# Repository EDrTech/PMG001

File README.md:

# PMG001 Power management module

The PMG001 is a highly integrated module designed for efficient management of single-cell
Li-Po battery systems. It incorporates various essential ICs to address all aspects of power
management, including battery charging, switch/button power on/off behavior, undervoltage
and overvoltage protection, flexible voltage measurement, battery current measurement, and
temperature monitoring. Additionally, it features a microcontroller for programming custom
behaviors, ensuring comprehensive management of single-cell rechargeable battery
systems.
Furthermore, when paired with the demo kit base PCB, the module serves as a general
development board for the ATTINY1616, with all
1 pins accessible for any application.

## Features

- 32 PIN 22.22mm *16.51mm package
- On/off behavior control
- 2A single cell charger
- Single li-po cell powered
- 4+16 ADC channels
- Bi-directional battery current measurement
- Brown-out detection/reset circuit
- Low RDSon battery output MOSFET
- On-module temperature measurement
- I2C Interface
- Arduino compatible

## Installation

To program this module you will need the following:

- Arduino DE (Or other IDE of your choosing)
- [megaTinyCore](https://github.com/SpenceKonde/megaTinyCore)
- Demo kit with the module soldered on

There's no need to install any additional libraries as the example code only uses the wire library to handle I2C, the rest is in the [example](pmg001_default/pmg001_default.ino) code. Keep in mind that some register values are hardcoded, which is not the best way to handle something like that but is done here for the sake of simplicity. You can use external libraries with this module without issues, you just need to redefine I2C adresses of devices as they don't necessarily match with other libraries.

Board settings should be set up like this:

Default code provides basic power management and monitoring - press PWR_SW for >500ms and BAT_OUT will turn on, hold PWR_SW for >3s and BAT_OUT will turn off.

For more information, please read the [datasheet](PMG001_datasheet.pdf).

## Module Schematic

## Breakout board Schematic

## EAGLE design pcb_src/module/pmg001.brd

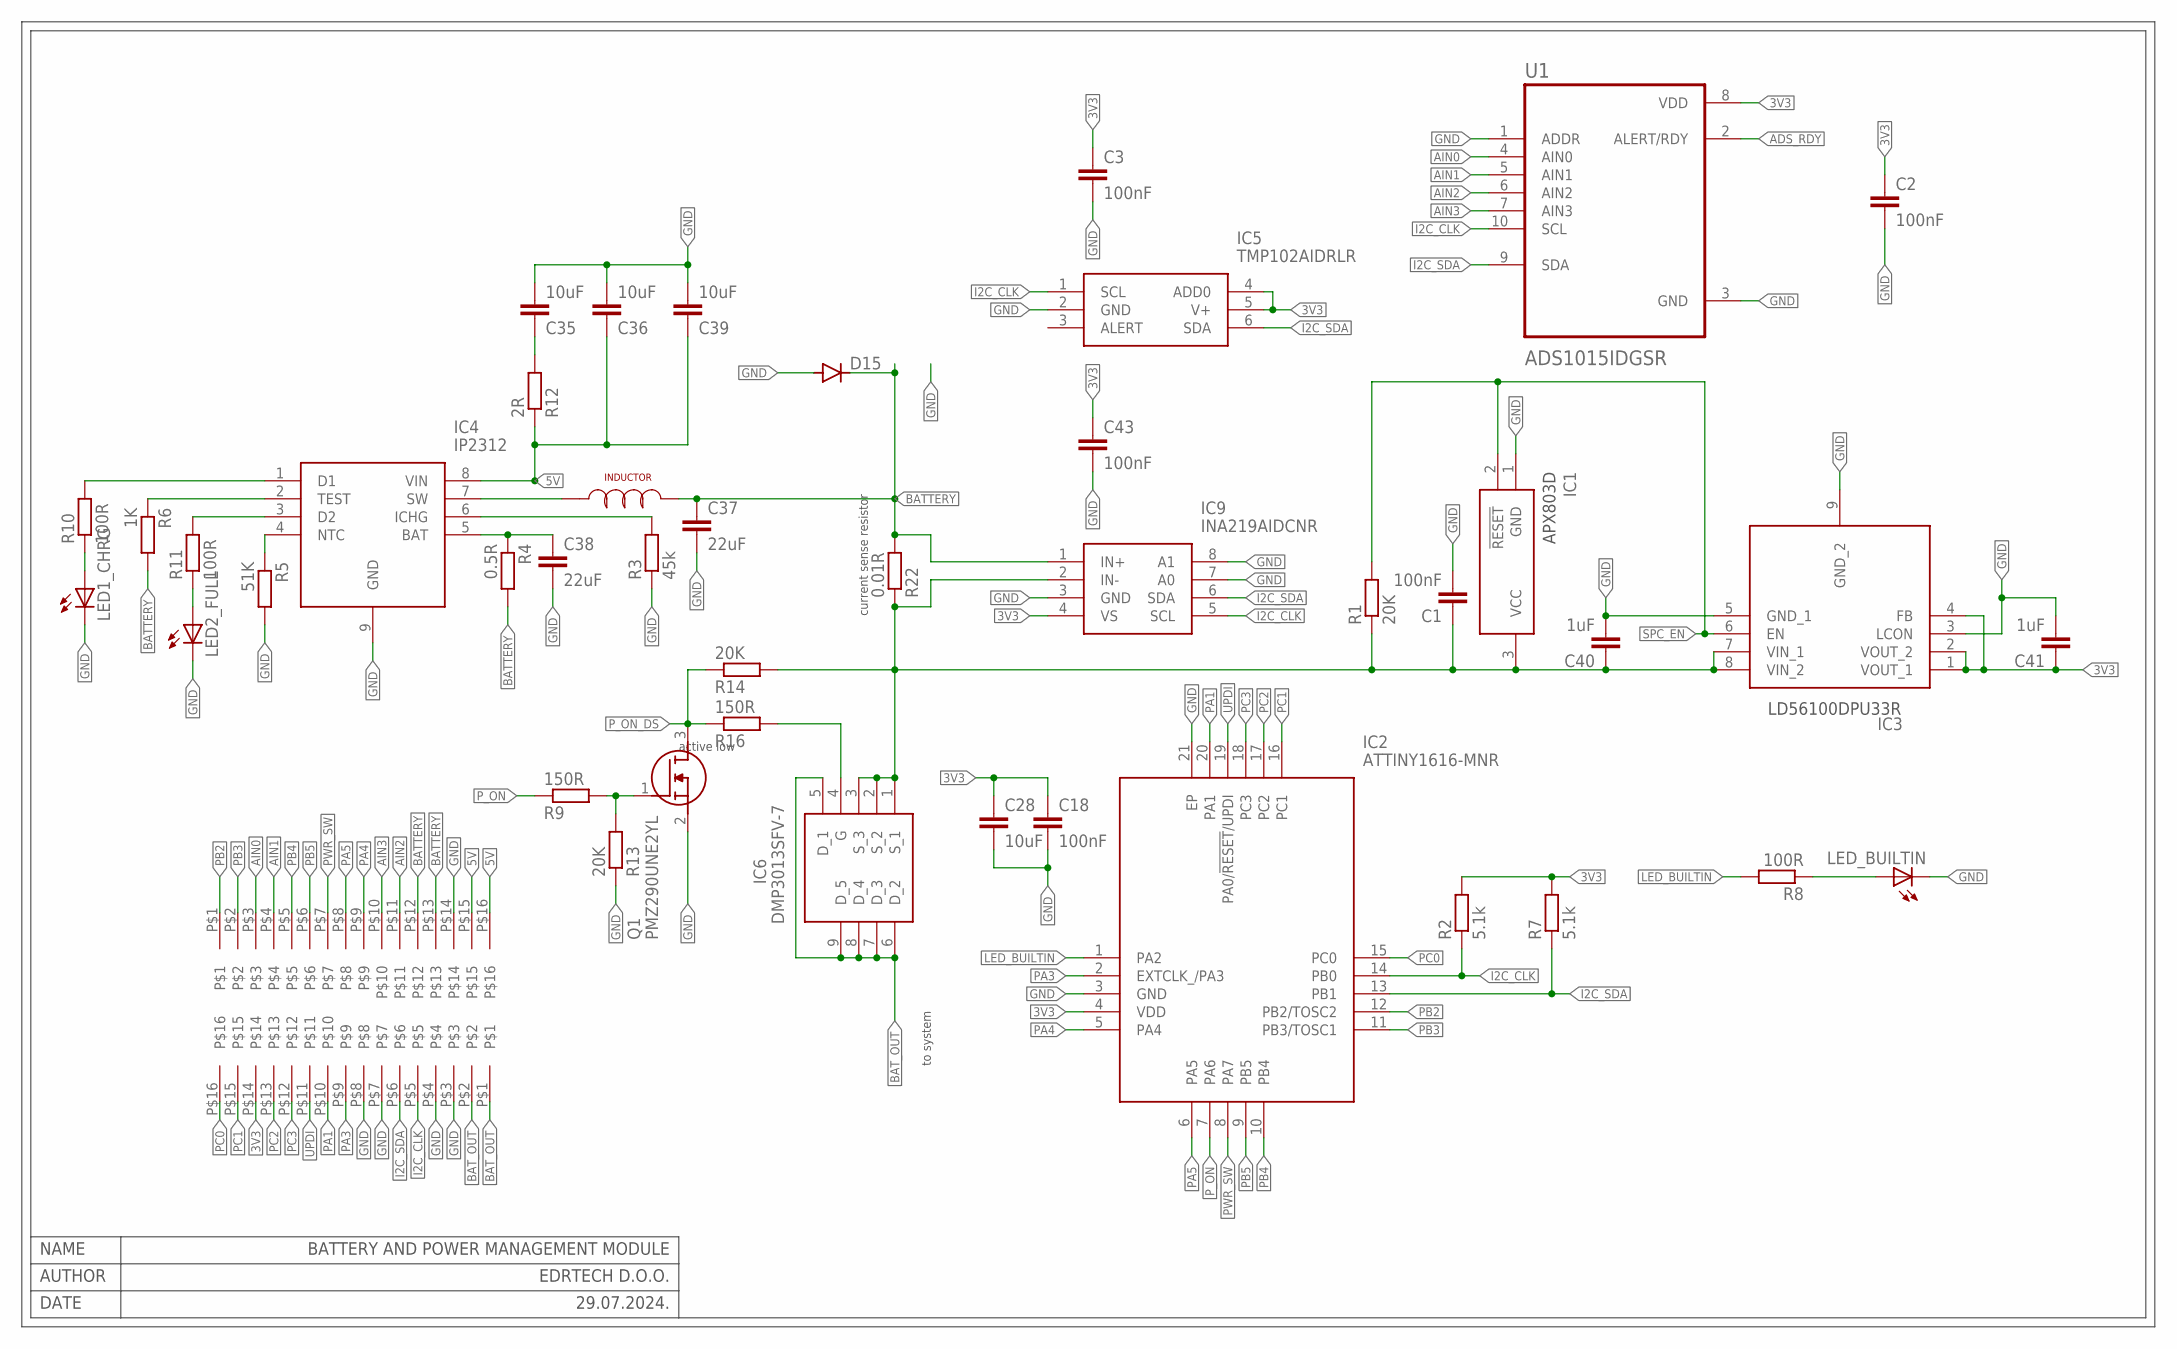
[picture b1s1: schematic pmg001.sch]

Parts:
C1, C2, C3, C18, C43: 100nF; C0402
C28: 10uF; C0402
C35, C36, C39: 10uF; C0603
C37, C38: 22uF; C0603
C40, C41: 1uF; C0402
D15: DIODE-SOD523; SOD523
IC1: APX803D-29SAG-7; SOT96P240X110-3N
IC2: ATTINY1616-MNR; QFN40P300X300X90-21N
IC3: LD56100DPU30R; SON40P120X160X50-9N
IC4: IP2312; SOIC127P600X165-9N
IC5: TMP102AIDRLR; SOTFL50P160X60-6N
IC6: DMP3013SFV-7; DMP3036SFV7
IC9: INA219AIDCNR; SOP65P280X145-8N
LED1_CHRG, LED2_FULL: LEDCHIPLED_0603; CHIPLED_0603
LED_BUILTIN: LEDCHIPLED_0603; CHIPLED_0603
Q1: PMZ290UNE2YL
R1, R13, R14: 20K; R0402
R2, R7: 5.1k; R0402
R3: 45k; R0402
R4: 0.5R; R0402
R5: 51K; R0402
R6: 1K; R0402
R8, R10, R11: 100R; R0402
R9, R16: 150R; R0402
R12: 2R; R0402
R22: 0.01R; R2512
U1: ADS1015IDGSR; SOP50P490X110-10N
U$1, U$2: 1.27_MALE_16P_HEADER
U$91: 1uH; NRS5040T3R3NMGJ

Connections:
3V3: C2.1, C3.1, C18.1, C28.1, C41.1, C43.1, IC2.4 (VDD), IC3.1 (VOUT_1), IC3.2 (VOUT_2), IC3.4 (FB), IC5.4 (ADD0), IC5.5 (V+), IC9.4 (VS), R2.2, R7.2, U1.8 (VDD), U$2.P$14
5V: C36.1, C39.1, IC4.8 (VIN), R12.1, U$1.P$15, U$1.P$16
ADS_RDY: U1.2 (ALERT/RDY)
AIN0: U1.4 (AIN0), U$1.P$3
AIN1: U1.5 (AIN1), U$1.P$4
AIN2: U1.6 (AIN2), U$1.P$11
AIN3: U1.7 (AIN3), U$1.P$10
BATTERY: C37.1, D15.C, IC9.1 (IN+), R4.2, R6.2, R22.2, U$1.P$12, U$1.P$13, U$91.P$1
BAT_OUT: IC6.5 (D_1), IC6.6 (D_2), IC6.7 (D_3), IC6.8 (D_4), IC6.9 (D_5), U$2.P$1, U$2.P$2
BTAP: C1.1, C40.1, IC1.3 (VCC), IC3.7 (VIN_1), IC3.8 (VIN_2), IC6.1 (S_1), IC6.2 (S_2), IC6.3 (S_3), IC9.2 (IN-), R1.1, R14.2, R22.1
GND: C1.2, C2.2, C3.2, C18.2, C28.2, C35.2, C36.2, C37.2, C38.2, C39.2, C40.2, C41.2, C43.2, D15.A, IC1.1 (GND), IC2.3 (GND), IC2.21 (EP), IC3.3 (LCON), IC3.5 (GND_1), IC3.9 (GND_2), IC4.9 (GND), IC5.2 (GND), IC9.3 (GND), IC9.7 (A0), IC9.8 (A1), LED1_CHRG.C, LED2_FULL.C, LED_BUILTIN.C, Q1.2 (S), R3.1, R5.2, R13.1, U1.1 (ADDR), U1.3 (GND), U$1.P$14, U$2.P$3, U$2.P$4, U$2.P$7, U$2.P$8
I2C_CLK: IC2.14 (PB0), IC5.1 (SCL), IC9.5 (SCL), R2.1, U1.10 (SCL), U$2.P$5
I2C_SDA: IC2.13 (PB1), IC5.6 (SDA), IC9.6 (SDA), R7.1, U1.9 (SDA), U$2.P$6
LED_BUILTIN: IC2.1 (PA2), R8.2
unnamed: Q1.1 (G), R9.2, R13.2
unnamed: LED_BUILTIN.A, R8.1
unnamed: IC6.4 (G), R16.2
unnamed: IC4.6 (ICHG), R3.2
unnamed: C35.1, R12.2
unnamed: LED1_CHRG.A, R10.1
unnamed: LED2_FULL.A, R11.1
unnamed: IC4.4 (NTC), R5.1
unnamed: IC4.2 (TEST), R6.1
unnamed: IC4.1 (D1), R10.2
unnamed: IC4.3 (D2), R11.2
unnamed: C38.1, IC4.5 (BAT), R4.1
unnamed: IC4.7 (SW), U$91.P$2
PA1: IC2.20 (PA1), U$2.P$10
PA3: IC2.2 (EXTCLK_/PA3), U$2.P$9
PA4: IC2.5 (PA4), U$1.P$9
PA5: IC2.6 (PA5), U$1.P$8
PB2: IC2.12 (PB2/TOSC2), U$1.P$1
PB3: IC2.11 (PB3/TOSC1), U$1.P$2
PB4: IC2.10 (PB4), U$1.P$5
PB5: IC2.9 (PB5), U$1.P$6
PC0: IC2.15 (PC0), U$2.P$16
PC1: IC2.16 (PC1), U$2.P$15
PC2: IC2.17 (PC2), U$2.P$13
PC3: IC2.18 (PC3), U$2.P$12
PWR_SW: IC2.8 (PA7), U$1.P$7
P_ON: IC2.7 (PA6), R9.1
P_ON_DS: Q1.3 (D), R14.1, R16.1
SPC_EN: IC1.2 (!RESET), IC3.6 (EN), R1.2
UPDI: IC2.19 (PA0/!RESET!/UPDI), U$2.P$11

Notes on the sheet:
BATTERY AND POWER MANAGEMENT MODULE
NAME
AUTHOR
DATE
EDRTECH D.O.O.
29.07.2024.
active low
current sense resistor
to system
LD56100DPU33R
APX803D

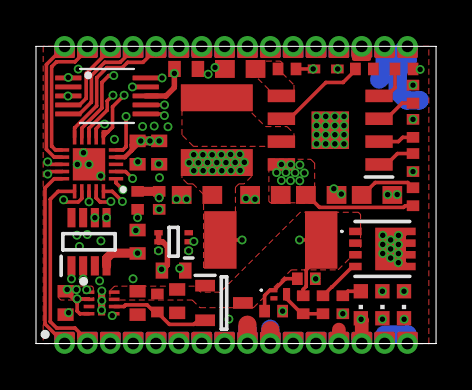
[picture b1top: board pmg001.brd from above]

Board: 6 copper layers, 22.2 x 16.5 mm, 45 parts (0 on the bottom side), 43 nets.

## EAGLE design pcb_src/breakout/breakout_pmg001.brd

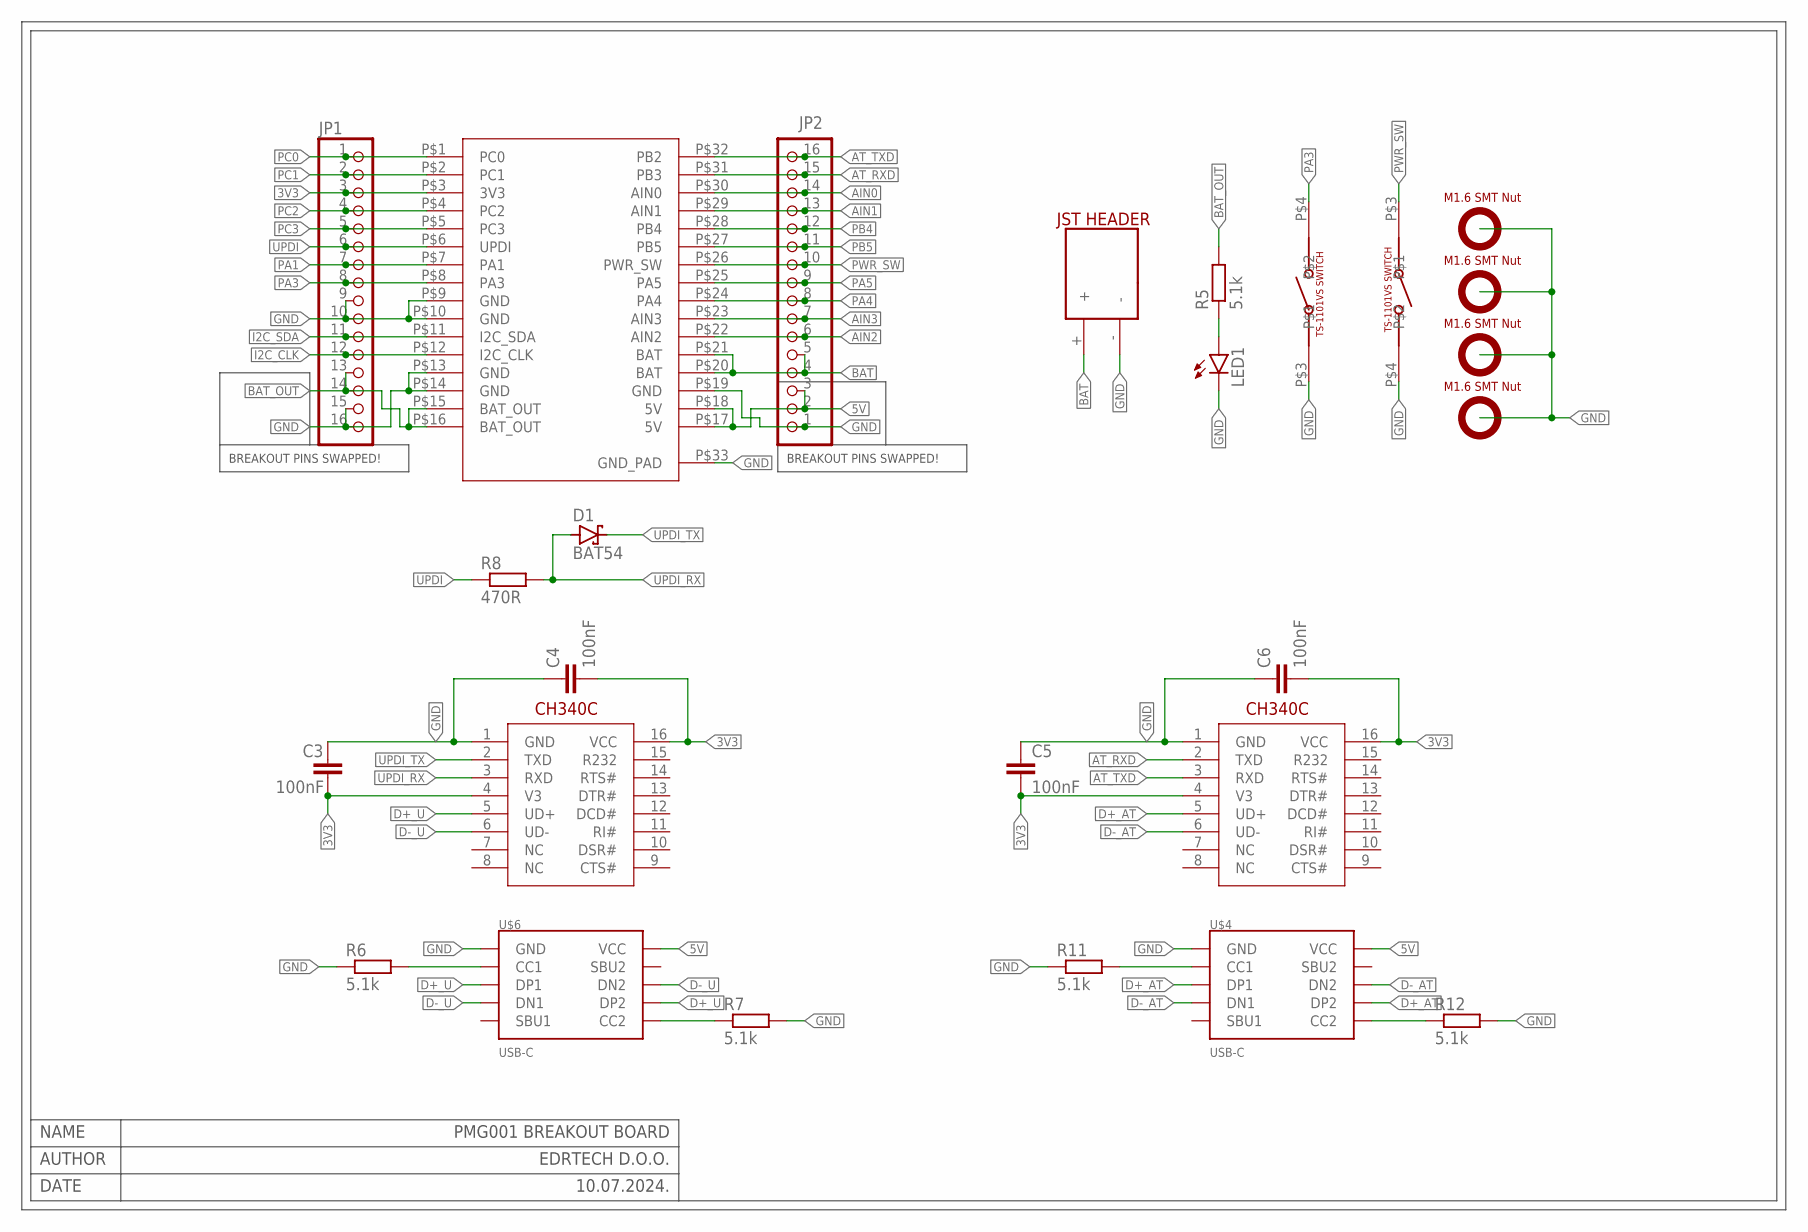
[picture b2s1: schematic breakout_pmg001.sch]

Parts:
C3, C4, C5, C6: 100nF; C0603
D1: BAT54; SOT23
JP1, JP2: PINHD-1X16; 1X16
LED1: LEDCHIPLED_1206; CHIPLED_1206
R5, R6, R7, R11, R12: 5.1k; R0603
R8: 470R; R0603
SPEAKER_CON1: JST_HEADER_2MM_2P; JST_HEADER
U$1, U$5: CH340C
U$2, U$3: TS-1101VS-C-A-A
U$4, U$6: USB-C
U$7: PMG001
U$8, U$9, U$10, U$11: SMTSO16

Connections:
3V3: C3.2, C4.2, C5.2, C6.2, JP1.3, U$1.4 (V3), U$1.16 (VCC), U$5.4 (V3), U$5.16 (VCC), U$7.P$3 (3V3)
5V: JP2.2, JP2.3, U$4.VCC@1 (VCC), U$4.VCC@2 (VCC), U$6.VCC@1 (VCC), U$6.VCC@2 (VCC), U$7.P$17 (5V), U$7.P$18 (5V)
AIN0: JP2.14, U$7.P$30 (AIN0)
AIN1: JP2.13, U$7.P$29 (AIN1)
AIN2: JP2.6, U$7.P$22 (AIN2)
AIN3: JP2.7, U$7.P$23 (AIN3)
AT_RXD: JP2.15, U$1.2 (TXD), U$7.P$31 (PB3)
AT_TXD: JP2.16, U$1.3 (RXD), U$7.P$32 (PB2)
BAT: JP2.4, JP2.5, SPEAKER_CON1.+, U$7.P$20 (BAT), U$7.P$21 (BAT)
BAT_OUT: JP1.13, JP1.14, R5.2, U$7.P$15 (BAT_OUT), U$7.P$16 (BAT_OUT)
D+_AT: U$1.5 (UD+), U$4.DP1, U$4.DP2
D+_U: U$5.5 (UD+), U$6.DP1, U$6.DP2
D-_AT: U$1.6 (UD-), U$4.DN1, U$4.DN2
D-_U: U$5.6 (UD-), U$6.DN1, U$6.DN2
GND: C3.1, C4.1, C5.1, C6.1, JP1.9, JP1.10, JP1.15, JP1.16, JP2.1, LED1.C, R6.1, R7.2, R11.1, R12.2, SPEAKER_CON1.-, U$1.1 (GND), U$2.P$3, U$3.P$4, U$4.GND@1 (GND), U$4.GND@2 (GND), U$4.P$1 (GND), U$4.P$2 (GND), U$4.P$3 (GND), U$4.P$4 (GND), U$5.1 (GND), U$6.GND@1 (GND), U$6.GND@2 (GND), U$6.P$1 (GND), U$6.P$2 (GND), U$6.P$3 (GND), U$6.P$4 (GND), U$7.P$9 (GND), U$7.P$10 (GND), U$7.P$13 (GND), U$7.P$14 (GND), U$7.P$19 (GND), U$7.P$33 (GND_PAD), U$8.P$1, U$9.P$1, U$10.P$1, U$11.P$1
I2C_CLK: JP1.12, U$7.P$12 (I2C_CLK)
I2C_SDA: JP1.11, U$7.P$11 (I2C_SDA)
unnamed: LED1.A, R5.1
unnamed: R6.2, U$6.CC1
unnamed: R7.1, U$6.CC2
unnamed: R11.2, U$4.CC1
unnamed: R12.1, U$4.CC2
PA1: JP1.7, U$7.P$7 (PA1)
PA3: JP1.8, U$2.P$4, U$7.P$8 (PA3)
PA4: JP2.8, U$7.P$24 (PA4)
PA5: JP2.9, U$7.P$25 (PA5)
PB4: JP2.12, U$7.P$28 (PB4)
PB5: JP2.11, U$7.P$27 (PB5)
PC0: JP1.1, U$7.P$1 (PC0)
PC1: JP1.2, U$7.P$2 (PC1)
PC2: JP1.4, U$7.P$4 (PC2)
PC3: JP1.5, U$7.P$5 (PC3)
PWR_SW: JP2.10, U$3.P$3, U$7.P$26 (PWR_SW)
UPDI: JP1.6, R8.1, U$7.P$6 (UPDI)
UPDI_RX: D1.1 (A), R8.2, U$5.3 (RXD)
UPDI_TX: D1.3 (C), U$5.2 (TXD)

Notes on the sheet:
PMG001 BREAKOUT BOARD
NAME
AUTHOR
DATE
EDRTECH D.O.O.
10.07.2024.
BREAKOUT PINS SWAPPED!

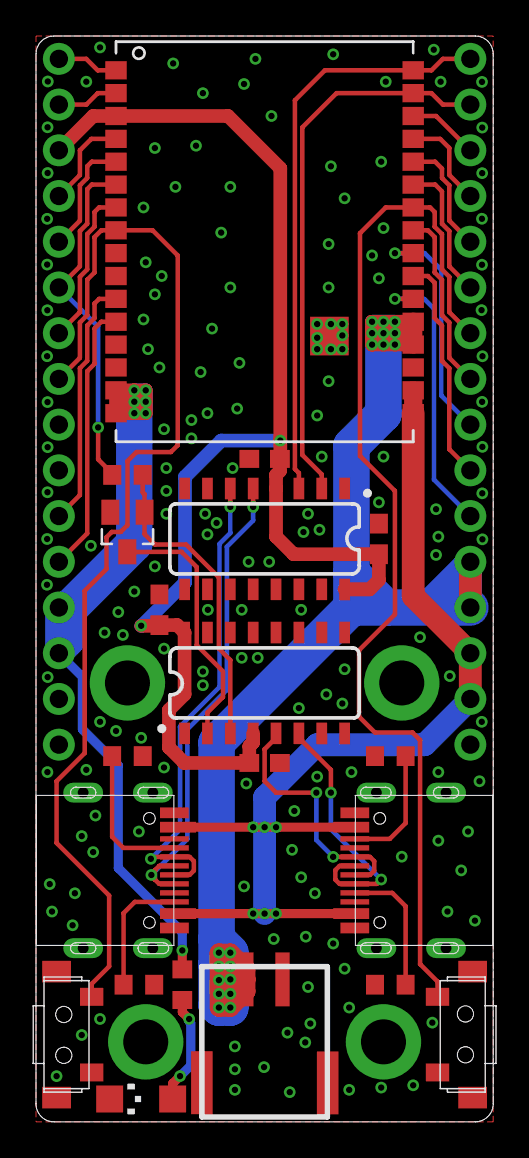
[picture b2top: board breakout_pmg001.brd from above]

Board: 2 copper layers, 25.4 x 60.3 mm, 26 parts (0 on the bottom side), 36 nets.

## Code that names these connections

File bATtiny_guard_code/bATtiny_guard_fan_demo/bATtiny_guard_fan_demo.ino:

#include <avr/sleep.h>
#include <avr/interrupt.h>
#include <Wire.h>
#include <megaTinyCore.h>

#define FAN_PIN     PIN_PA6

#define SW1_PIN     PIN_PA3
#define SW2_PIN     PIN_PC2
#define RESET_PIN   PIN_PC3

#define LED_FAULT_PIN  PIN_PA1
#define LED_WARN_PIN   PIN_PA4
#define LED_OK_PIN     PIN_PA5

#define INA219_ADDRESS 0x40
#define TMP102_ADDRESS 0x49
#define ADS1015_ADDRESS 0x48

bool fan_enabled = false;
bool fault_active = false;

float current_threshold = 160.0f;

float currentBuffer[3] = {0};
uint8_t currentIndex = 0;
bool bufferFilled = false;

unsigned long fanStartTime = 0;

bool sw1Prev = true;
bool sw2Prev = true;
bool resetPrev = true;

unsigned long lastReport = 0;
const unsigned long reportInterval = 1000;

void INA219_setCal() 
{
  uint16_t calByte = 4096;
  uint16_t configBytes = 0b0011100110011111;

  Wire.beginTransmission(INA219_ADDRESS);
  Wire.write(0x05);
  Wire.write((uint8_t)(calByte >> 8));
  Wire.write((uint8_t)(calByte & 0xFF));
  Wire.endTransmission();

  Wire.beginTransmission(INA219_ADDRESS);
  Wire.write(0x00);
  Wire.write((uint8_t)(configBytes >> 8));
  Wire.write((uint8_t)(configBytes & 0xFF));
  Wire.endTransmission();
}

float INA219_readBV() 
{
  uint16_t busVoltReg = 0x00;
  INA219_setCal();

  Wire.beginTransmission(INA219_ADDRESS);
  Wire.write(0x02);
  Wire.endTransmission();

  Wire.requestFrom(INA219_ADDRESS, 2);
  if (Wire.available() == 2) 
  {
    busVoltReg = (Wire.read() << 8) | Wire.read();
  }

  return ((busVoltReg >> 3) * 0.001) * 4;
}

float INA219_readSV() 
{
  uint16_t shuntVoltReg = 0x00;
  INA219_setCal();

  Wire.beginTransmission(INA219_ADDRESS);
  Wire.write(0x01);
  Wire.endTransmission();

  Wire.requestFrom(INA219_ADDRESS, 2);
  if (Wire.available() == 2) {
    shuntVoltReg = (Wire.read() << 8) | Wire.read();
  }

  return shuntVoltReg * 0.1;
}

float INA219_readC() 
{
  uint16_t currentReg = 0x00;
  INA219_setCal();

  Wire.beginTransmission(INA219_ADDRESS);
  Wire.write(0x04);
  Wire.endTransmission();

  Wire.requestFrom(INA219_ADDRESS, 2);
  if (Wire.available() == 2) 
  {
    currentReg = (Wire.read() << 8) | Wire.read();
  }

  return currentReg;
}

float readTMP102() 
{
  int16_t dTemp;
  Wire.beginTransmission(TMP102_ADDRESS);
  Wire.write(0x00);
  Wire.endTransmission();

  uint8_t regByte[2];
  Wire.requestFrom(TMP102_ADDRESS, 2);
  regByte[0] = Wire.read();
  regByte[1] = Wire.read();

  dTemp = ((regByte[0]) << 4) | (regByte[1] >> 4);
  if (dTemp > 0x7FF) 
  {
    dTemp |= 0xF000;
  }
  return dTemp * 0.0625;
}

float ADS1015_readChannel(uint8_t channel) 
{
  uint16_t mux;
  switch (channel) 
  {
    case 0: mux = 0x4000; break;
    case 1: mux = 0x5000; break;
    case 2: mux = 0x6000; break;
    case 3: mux = 0x7000; break;
    default: return -1;
  }

  uint16_t configBytes = 0x0000 | 0x0200 | mux | 0x0080 | 0x8000;
  uint16_t voltReg = 0x00;

  Wire.beginTransmission(ADS1015_ADDRESS);
  Wire.write(0x01);
  Wire.write((uint8_t)(configBytes >> 8));
  Wire.write((uint8_t)(configBytes & 0xFF));
  Wire.endTransmission();

  delay(10);

  Wire.beginTransmission(ADS1015_ADDRESS);
  Wire.write(0x00);
  Wire.endTransmission();

  Wire.requestFrom(ADS1015_ADDRESS, 2);
  if (Wire.available() == 2) 
  {
    voltReg = (Wire.read() << 8) | Wire.read();
  }

  return (voltReg >> 4) * (4.096f / (32768 >> 4));
}

void setup() 
{
  Serial.begin(115200);
  Wire.begin();

  pinMode(FAN_PIN, OUTPUT);
  digitalWrite(FAN_PIN, LOW);

  pinMode(SW1_PIN, INPUT_PULLUP);
  pinMode(SW2_PIN, INPUT_PULLUP);
  pinMode(RESET_PIN, INPUT_PULLUP);

  pinMode(LED_OK_PIN, OUTPUT);
  pinMode(LED_WARN_PIN, OUTPUT);
  pinMode(LED_FAULT_PIN, OUTPUT);

  digitalWrite(LED_OK_PIN, LOW);
  digitalWrite(LED_WARN_PIN, LOW);
  digitalWrite(LED_FAULT_PIN, LOW);
}

void loop() 
{
  float current_mA = INA219_readC();
  float bvbuf = INA219_readBV();
  float svbuf = INA219_readSV();
  float tbuf = readTMP102();
  float pot_voltage = ADS1015_readChannel(2);

  if (pot_voltage >= 0.0f && pot_voltage <= 3.3f) 
  {
    current_threshold = 160.0f + ((pot_voltage / 3.3f) * (250.0f - 160.0f));
  }

  bool sw1Now = digitalRead(SW1_PIN);
  bool sw2Now = digitalRead(SW2_PIN);
  bool resetNow = digitalRead(RESET_PIN);

  if (sw1Prev && !sw1Now && !fault_active) 
  {
    fan_enabled = !fan_enabled;
    if (fan_enabled) 
    {
      fanStartTime = millis();
    }
  }
  if (sw2Prev && !sw2Now && !fault_active) 
  {
    fan_enabled = !fan_enabled;
    if (fan_enabled) 
    {
      fanStartTime = millis();
    }
  }

  if (resetPrev && !resetNow) 
  {
    fault_active = false;
    digitalWrite(LED_FAULT_PIN, LOW);
  }

  sw1Prev = sw1Now;
  sw2Prev = sw2Now;
  resetPrev = resetNow;

  digitalWrite(FAN_PIN, fan_enabled ? HIGH : LOW);

  currentBuffer[currentIndex] = current_mA;
  currentIndex = (currentIndex + 1) % 3;
  if (currentIndex == 0) bufferFilled = true;

  float avg_current = 0.0;
  int count = bufferFilled ? 3 : currentIndex;
  for (int i = 0; i < count; ++i) 
  {
    avg_current += currentBuffer[i];
  }
  avg_current /= count;

  bool ignore_current = (millis() - fanStartTime < 1000);

  if (fan_enabled && !fault_active) 
  {
    if (!ignore_current) 
    {
      if (avg_current < 120.0f) 
      {
        digitalWrite(LED_OK_PIN, HIGH);
        digitalWrite(LED_WARN_PIN, LOW);
        digitalWrite(LED_FAULT_PIN, LOW);
      }
      else if (avg_current < current_threshold) 
      {
        digitalWrite(LED_OK_PIN, HIGH);
        digitalWrite(LED_WARN_PIN, HIGH);
        digitalWrite(LED_FAULT_PIN, LOW);
      } else 
      {
        fault_active = true;
        fan_enabled = false;
        digitalWrite(FAN_PIN, LOW);
        digitalWrite(LED_FAULT_PIN, HIGH);
        digitalWrite(LED_OK_PIN, LOW);
        digitalWrite(LED_WARN_PIN, LOW);
      }
    } 
    else 
    {
      digitalWrite(LED_OK_PIN, HIGH);
      digitalWrite(LED_WARN_PIN, LOW);
      digitalWrite(LED_FAULT_PIN, LOW);
    }
  }

  if (!fan_enabled) 
  {
    digitalWrite(LED_OK_PIN, LOW); // Turn off green LED when fan is off
    digitalWrite(LED_WARN_PIN, LOW);
  }

  if (millis() - lastReport > reportInterval) 
  {
    lastReport = millis();
    Serial.write(12);  // Clear terminal

    Serial.println(F("==================================="));
    Serial.print(F("TMP102 Temperature:      ")); Serial.print(tbuf, 2); Serial.println(F("°C"));
    Serial.println(F("-----------------------------------"));
    Serial.print(F("ADS1015 AIN2 (POT):      ")); Serial.println(pot_voltage, 4);
    Serial.print(F("Current Threshold:       ")); Serial.print(current_threshold, 1); Serial.println(F(" mA"));
    Serial.println(F("-----------------------------------"));
    Serial.print(F("INA219 Battery voltage:  ")); Serial.print(bvbuf, 4); Serial.println(F(" V"));
    Serial.print(F("INA219 Battery current:  ")); Serial.print(current_mA, 4); Serial.println(F(" mA"));
    Serial.print(F("Avg Current (3 samples): ")); Serial.print(avg_current, 4); Serial.println(F(" mA"));
    Serial.println(F("-----------------------------------"));
    Serial.print(F("PA3_SW:   ")); Serial.println(!sw1Now);
    Serial.print(F("PC2_SW:   ")); Serial.println(!sw2Now);
    Serial.print(F("PC3_RESET:")); Serial.println(!resetNow);
    Serial.print(F("FAN_OUT:  ")); Serial.println(digitalRead(FAN_PIN));
    Serial.print(F("LED_OK:   ")); Serial.println(digitalRead(LED_OK_PIN));
    Serial.print(F("LED_WARN: ")); Serial.println(digitalRead(LED_WARN_PIN));
    Serial.print(F("LED_FAULT:")); Serial.println(digitalRead(LED_FAULT_PIN));
    Serial.println(F("==================================="));
  }
}

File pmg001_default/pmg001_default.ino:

#include <avr/sleep.h>
#include <avr/interrupt.h>
#include <Wire.h>

#define INA219_ADDRESS 0x40
#define TMP102_ADDRESS 0x49
#define ADS1015_ADDRESS 0x48

volatile uint16_t pa7_timer_count = 0;
volatile uint16_t pa3_timer_count = 0;
volatile bool pa7_pressed = false;
volatile bool pa3_pressed = false;
volatile bool pa7_handled = false;
volatile bool pa3_handled = false;

void setup() {
  Serial.begin(115200);
  while (RTC.STATUS > 0)
    {
        ;  // Wait for all registers to be synchronized
    }
  RTC.CLKSEL = RTC_CLKSEL_INT32K_gc;  // 32.768kHz Internal Ultra-Low-Power Oscillator (OSCULP32K)
  RTC.PITINTCTRL = RTC_PI_bm;  // PIT Interrupt: enabled
  RTC.PITCTRLA = RTC_PERIOD_CYC32768_gc | RTC_PITEN_bm;  // Enable PIT counter: enabled 

  PORTA.DIRCLR = PIN7_bm | PIN3_bm;  
  PORTA.PIN7CTRL = PORT_PULLUPEN_bm | PORT_ISC_BOTHEDGES_gc;
  PORTA.PIN3CTRL = PORT_PULLUPEN_bm | PORT_ISC_BOTHEDGES_gc;

  PORTA.DIRSET = PIN2_bm | PIN6_bm;
  PORTA.OUTCLR = PIN2_bm;  // PA2 initially off
  PORTA.OUTCLR = PIN6_bm;  // PA6 initially off

  cli();

  takeOverTCA0();  // Ensure control of TCA0 timer

  // Configure TCA0 for 100ms interval
  TCA0.SINGLE.CTRLA = TCA_SINGLE_CLKSEL_DIV64_gc;  
  TCA0.SINGLE.PER = 1562;  // 100ms with 10MHz clock and 64 prescaler
  TCA0.SINGLE.CTRLA |= TCA_SINGLE_ENABLE_bm; // Enable the timer
  TCA0.SINGLE.INTCTRL = TCA_SINGLE_OVF_bm;   // Enable overflow interrupt

  sei();
  Wire.begin();
  set_sleep_mode(SLEEP_MODE_STANDBY);  // Set sleep mode to standby
}

void loop() {
  // Enter standby mode when idle
  if (!pa7_pressed && !pa3_pressed) {
    sleep_mode();  // Enter standby mode
  }
}

ISR(PORTA_PORT_vect) {

  // Debounce delay
  delay(10);

  if (PORTA.INTFLAGS & PIN7_bm) {
    pa7_pressed = !(PORTA.IN & PIN7_bm); // LOW when pressed

    if (pa7_pressed) {
      pa7_timer_count = 0; // Start counting when button is pressed
      pa7_handled = false; // Reset action flag
    }
    PORTA.INTFLAGS = PIN7_bm;
  }

  if (PORTA.INTFLAGS & PIN3_bm) {
    pa3_pressed = !(PORTA.IN & PIN3_bm); // LOW when pressed

    if (pa3_pressed) {
      pa3_timer_count = 0; // Start counting when button is pressed
      pa3_handled = false; // Reset action flag
    }
    PORTA.INTFLAGS = PIN3_bm;
  }
  Serial.flush();
}

ISR(TCA0_OVF_vect) {
  TCA0.SINGLE.INTFLAGS = TCA_SINGLE_OVF_bm;

  // PA7 tracking
  if (pa7_pressed && !pa7_handled) {
    pa7_timer_count++;

    if (!(PORTA.OUT & PIN6_bm) && pa7_timer_count >= 20) { // PA6 is off, 200ms
      PORTA.OUTSET = PIN6_bm; // Turn PA6 on (LOW state)

      pa7_handled = true; // Mark action as handled
    } else if ((PORTA.OUT & PIN6_bm) && pa7_timer_count >= 300) { // PA6 is on, 3s
      PORTA.OUTCLR = PIN6_bm; // Turn PA6 off (HIGH state)

      pa7_handled = true; // Mark action as handled
    }
  }

  // PA3 tracking
  if (pa3_pressed && !pa3_handled) {
    pa3_timer_count++;

    if (pa3_timer_count >= 2) {  // 200ms
      PORTA.OUTTGL = PIN2_bm; // Toggle PA2
      pa3_handled = true; // Mark action as handled
    }
  }

  // Reset timer counts when buttons are released
  if (!pa7_pressed) {
    pa7_timer_count = 0;
  }
  if (!pa3_pressed) {
    pa3_timer_count = 0;
  }
}

ISR(RTC_PIT_vect) 
{
    RTC.PITINTFLAGS = RTC_PI_bm;  // Clear interrupt flag by writing '1' (required)
    float tbuf = readTMP102();
    float ain0buf = ADS1015_readChannel(0);
    float ain1buf = ADS1015_readChannel(1);
    float ain2buf = ADS1015_readChannel(2);
    float ain3buf = ADS1015_readChannel(3);
    float bvbuf = INA219_readBV();
    float svbuf = INA219_readSV();
    float bcbuf = INA219_readC();

    Serial.write(12);  // Clear screen and move cursor to home
     String output = "";  // Clear screen and move cursor to home
    output += "-----------------------------------\r\n";
    output += "TMP102 Temperature:      ";
    output += String(tbuf, 2);
    output += "°C\r\n";
    output += "-----------------------------------\r\n";
    output += "ADS1015 AIN0:            ";
    output += String(ain0buf, 4);
    output += "V\r\n";
    output += "ADS1015 AIN1:            ";
    output += String(ain1buf, 4);
    output += "V\r\n";
    output += "ADS1015 AIN2:            ";
    output += String(ain2buf, 4);
    output += "V\r\n";
    output += "ADS1015 AIN3:            ";
    output += String(ain3buf, 4);
    output += "V\r\n";
    output += "-----------------------------------\r\n";
    output += "INA219 Battery voltage:  ";
    output += String(bvbuf, 4);
    output += "V\r\n";
    output += "INA219 Shunt voltage:    ";
    output += String(svbuf, 4);
    output += "mV\r\n";
    output += "INA219 Battery current:  ";
    output += String(bcbuf, 4);
    output += "mA\r\n";
    output += "-----------------------------------\r\n";
    output += "PWR_SW:  ";
    output += String(!digitalRead(PIN_PA7));
    output += "\r\n";
    output += "PA3_SW:  ";
    output += String(!digitalRead(PIN_PA3));
    output += "\r\n";
    output += "BAT_OUT:  ";
    output += String(digitalRead(PIN_PA6));
    output += "\r\n";
    output += "LED_BUILTIN:  ";
    output += String(digitalRead(PIN_PA2));
    output += "\r\n";
    output += "-----------------------------------\r\n";
    Serial.print(output);

    Serial.flush();
}

void INA219_setCal() 
{
    uint16_t calByte = 4096;  // Calibration register value
    uint16_t configBytes = 0b0011100110011111;  // Configuration register value

    Wire.beginTransmission(INA219_ADDRESS);
    Wire.write(0x05);  // Calibration register address
    Wire.write((uint8_t)(calByte >> 8));  // High byte
    Wire.write((uint8_t)(calByte & 0xFF));  // Low byte
    Wire.endTransmission();

    Wire.beginTransmission(INA219_ADDRESS);
    Wire.write(0x00);  // Configuration register address
    Wire.write((uint8_t)(configBytes >> 8));  // High byte
    Wire.write((uint8_t)(configBytes & 0xFF));  // Low byte
    Wire.endTransmission();
}

float INA219_readBV() 
{
    uint16_t busVoltReg = 0x00;
    INA219_setCal();

    Wire.beginTransmission(INA219_ADDRESS);
    Wire.write(0x02);  // Bus voltage register address
    Wire.endTransmission();

    Wire.requestFrom(INA219_ADDRESS, 2);
    if (Wire.available() == 2) 
    {
        busVoltReg = (Wire.read() << 8) | Wire.read();
    }

    return ((busVoltReg >> 3) * 0.001) * 4;
}

float INA219_readSV() 
{
    uint16_t shuntVoltReg = 0x00;
    INA219_setCal();

    Wire.beginTransmission(INA219_ADDRESS);
    Wire.write(0x01);  // Shunt voltage register address
    Wire.endTransmission();

    Wire.requestFrom(INA219_ADDRESS, 2);
    if (Wire.available() == 2) 
    {
        shuntVoltReg = (Wire.read() << 8) | Wire.read();
    }

    return shuntVoltReg * 0.1;
}

float INA219_readC() 
{
    uint16_t currentReg = 0x00;
    INA219_setCal();

    Wire.beginTransmission(INA219_ADDRESS);
    Wire.write(0x04);  // Current register address
    Wire.endTransmission();

    Wire.requestFrom(INA219_ADDRESS, 2);
    if (Wire.available() == 2) 
    {
        currentReg = (Wire.read() << 8) | Wire.read();
    }

    return currentReg;
}

float readTMP102() 
{
    int16_t dTemp;
    Wire.beginTransmission(TMP102_ADDRESS);
    Wire.write(0X00);  // Temperature register address
    Wire.endTransmission();

    uint8_t regByte[2];
    Wire.requestFrom(TMP102_ADDRESS, 2);
    regByte[0] = Wire.read();
    regByte[1] = Wire.read();

    dTemp = ((regByte[0]) << 4) | (regByte[1] >> 4);
    if (dTemp > 0x7FF) 
    {
        dTemp |= 0xF000;
    }
    return dTemp * 0.0625;
}

float ADS1015_readChannel(uint8_t channel) 
{
    uint16_t mux;
    switch (channel) 
    {
        case 0: mux = 0x4000; break;
        case 1: mux = 0x5000; break;
        case 2: mux = 0x6000; break;
        case 3: mux = 0x7000; break;
        default: return -1;
    }

    uint16_t configBytes = 0x0000 | 0x0200 | mux | 0x0080 | 0x8000;
    uint16_t voltReg = 0x00;

    Wire.beginTransmission(ADS1015_ADDRESS);
    Wire.write(0x01);  // Configuration register address
    Wire.write((uint8_t)(configBytes >> 8));  // High byte
    Wire.write((uint8_t)(configBytes & 0xFF));  // Low byte
    Wire.endTransmission();

    delay(10);  // Wait for conversion to complete

    Wire.beginTransmission(ADS1015_ADDRESS);
    Wire.write(0x00);  // Conversion register address
    Wire.endTransmission();

    Wire.requestFrom(ADS1015_ADDRESS, 2);
    if (Wire.available() == 2) 
    {
        voltReg = (Wire.read() << 8) | Wire.read();
    }

    return (voltReg >> 4) * (4.096f / (32768 >> 4));
}

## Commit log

2024-07-16 Updated documentation
    Datasheet updated
    Visuals added
    FIle names changed
2024-07-16 Added BOMs
    BOM for module added
    Bom for demo kit added
2024-08-01 Module and cover board revised. Datasheet revised. Code added.
    Updated with one additional component, added cutout to cover board. Updated documentation accordingly. Added default program.
2024-08-01 I2C Adress corrected
    Corrected I2C address of ADS1015
2024-08-01 Updated readme.
2024-08-01 Added arduino ide board settings
2024-08-01 Added schematics
    white background
2024-08-05 Updated BOM
    Replaced/added some components
2024-08-24 Power saving features added
    Wake up from power down mode every 5 seconds to take measurements.
    Wake up on button interrupt.
    This realizes big power saving gains as the CPU is powered down most of the time.
2024-08-25 Added Symbol/footprint libraries
    EAGLE and KiCad
2024-08-26 Reworked firmware for power saving
    Now works almost exclusively based on interrupts, cpu is in standby mode to reduce power consumption when not running.
2024-08-30 Switched to Cern OHL-P License
2024-09-05 Updated firmware, added layers document
    Firmware updated to match hardware.
    Added PDF with PCB layers.
2025-06-06 Added KiCAD conversion
2025-06-13 Added fan current demo code
2025-06-13 Folder structure fixed
